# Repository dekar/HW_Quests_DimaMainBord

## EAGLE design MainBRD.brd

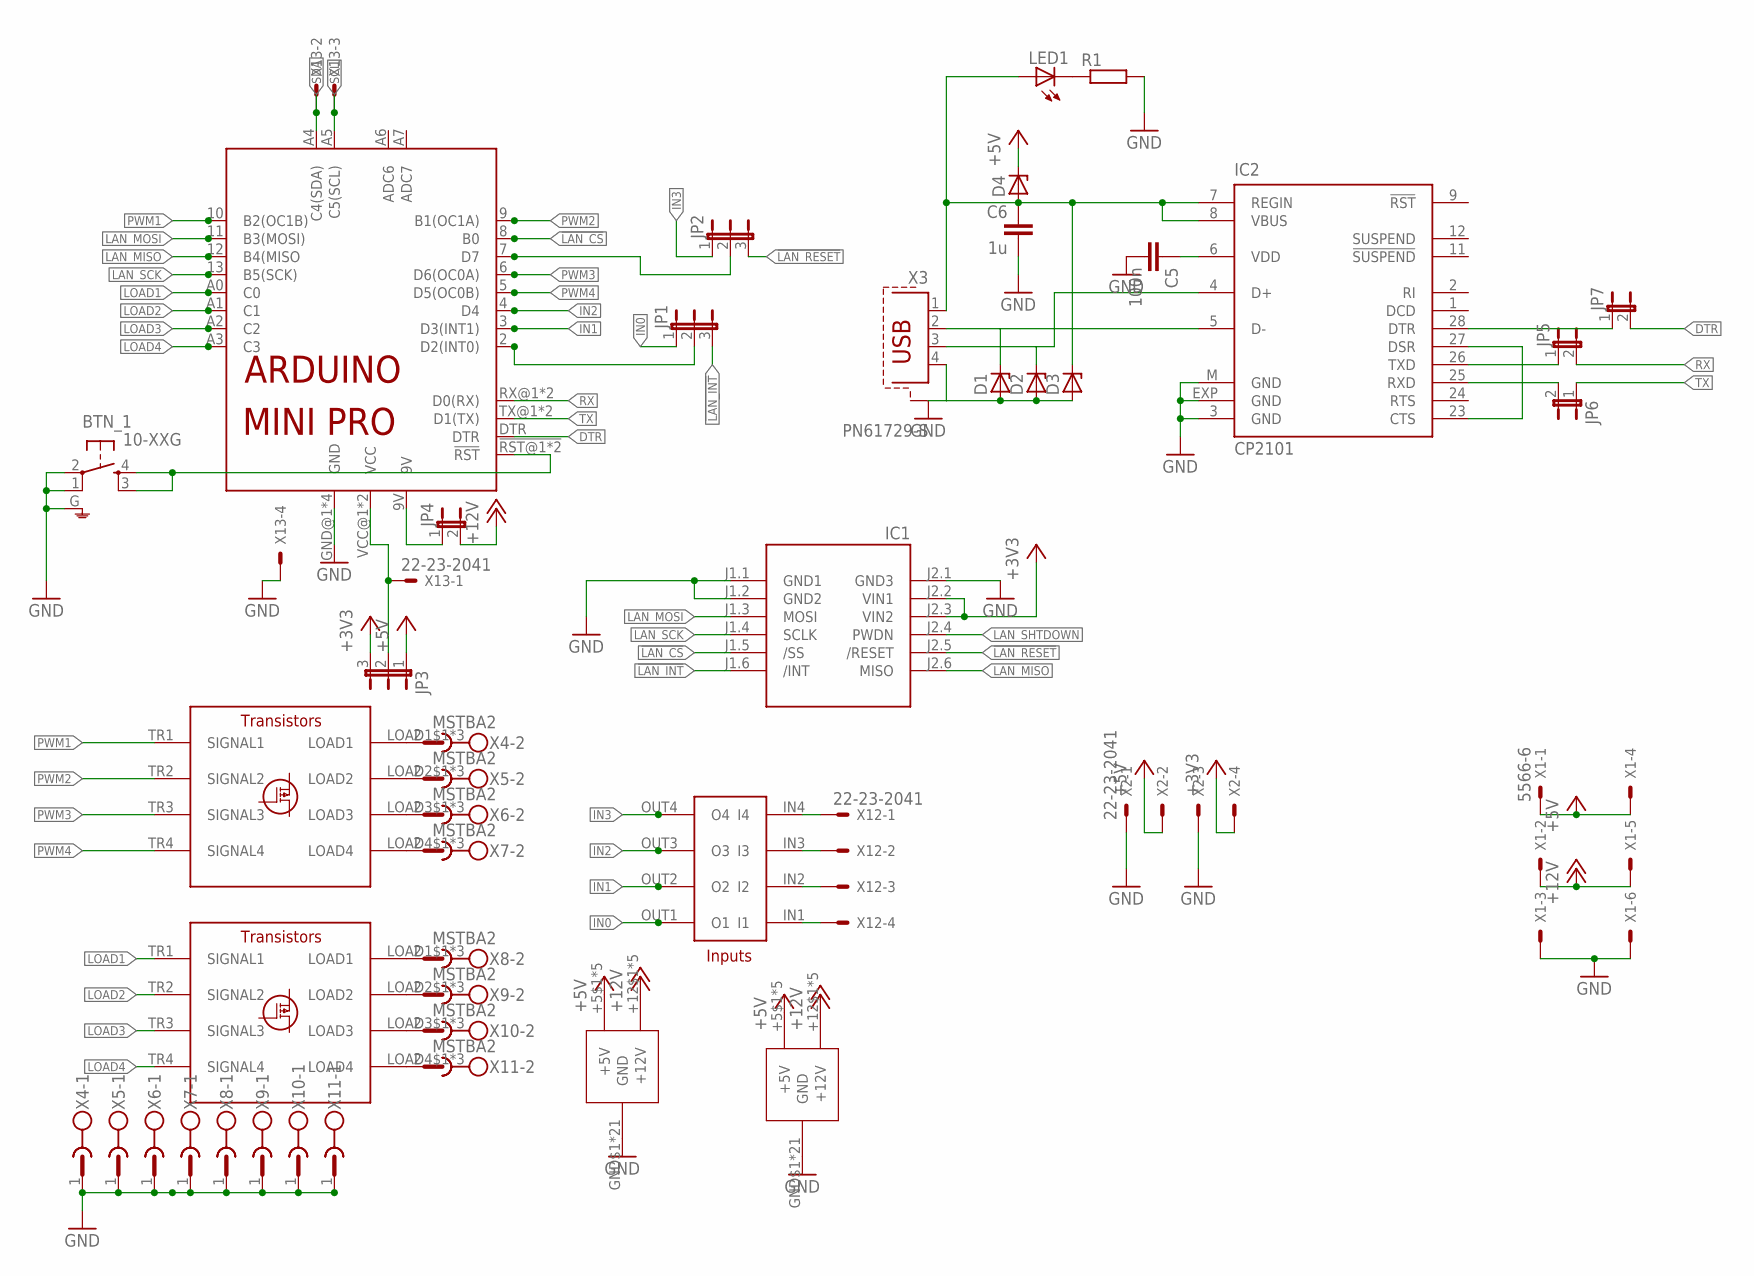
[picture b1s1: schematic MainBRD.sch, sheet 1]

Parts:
BTN_1: 10-XXG; B3F-10XXG
C5: 100n; C0805
C6: 1u; C1206
D1, D2, D3, D4: ZENER-DIODESOD80C; SOD80C
IC1: WIZ820IO_DEVICE'DUAL-IN-LINE'; WIZ820IO
IC2: CP2101; MLP28
JP1, JP2, JP3: JP2E; JP2
JP4, JP5, JP6, JP7: JP1E; JP1
LED1: LEDCHIPLED_1206; CHIPLED_1206
R1: R-EU_M0805; M0805
U$1: ARDUINO_MINI_PRO
U$2, U$3: KBLES_TRANSISTOR
X1: 5566-6
X2: 22-23-2041
X3: PN61729-S
X4: MSTBA2
X5, X6, X7, X8, X9, X10, X11: MSTBA2; MPN 1757242
X12, X13: 22-23-2041; MPN 22-23-2041

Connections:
!LAN_CS: IC1.J1.5 (/SS), U$1.8 (B0)
!LAN_INT: IC1.J1.6 (/INT), JP1.3
!LAN_RESET: IC1.J2.5 (/RESET), JP2.3
+3V3: IC1.J2.2 (VIN1), IC1.J2.3 (VIN2), JP3.3, X2.4
+5V: D4.C, JP3.1, U$2.+5$1 (+5V), U$2.+5$2 (+5V), U$2.+5$3 (+5V), U$2.+5$4 (+5V), U$2.+5$5 (+5V), U$3.+5$1 (+5V), U$3.+5$2 (+5V), U$3.+5$3 (+5V), U$3.+5$4 (+5V), U$3.+5$5 (+5V), X1.1, X1.4, X2.2
+12V: JP4.2, U$2.+12$1 (+12V), U$2.+12$2 (+12V), U$2.+12$3 (+12V), U$2.+12$4 (+12V), U$2.+12$5 (+12V), U$3.+12$1 (+12V), U$3.+12$2 (+12V), U$3.+12$3 (+12V), U$3.+12$4 (+12V), U$3.+12$5 (+12V), X1.2, X1.5
DSR/CTS: IC2.23 (CTS), IC2.27 (DSR)
DTR: JP7.2, U$1.DTR
GND: BTN_1.1, BTN_1.2, BTN_1.G (GND), C5.2, C6.2, D1.A, D2.A, D3.A, IC1.J1.1 (GND1), IC1.J1.2 (GND2), IC1.J2.1 (GND3), IC2.3 (GND), IC2.EXP (GND), IC2.M (GND), R1.2, U$1.GND@1 (GND), U$1.GND@2 (GND), U$1.GND@3 (GND), U$1.GND@4 (GND), U$2.GND$1 (GND), U$2.GND$2 (GND), U$2.GND$3 (GND), U$2.GND$4 (GND), U$2.GND$5 (GND), U$2.GND$6 (GND), U$2.GND$7 (GND), U$2.GND$8 (GND), U$2.GND$9 (GND), U$2.GND$10 (GND), U$2.GND$11 (GND), U$2.GND$12 (GND), U$2.GND$13 (GND), U$2.GND$14 (GND), U$2.GND$15 (GND), U$2.GND$16 (GND), U$2.GND$17 (GND), U$2.GND$18 (GND), U$2.GND$19 (GND), U$2.GND$20 (GND), U$2.GND$21 (GND), U$3.GND$1 (GND), U$3.GND$2 (GND), U$3.GND$3 (GND), U$3.GND$4 (GND), U$3.GND$5 (GND), U$3.GND$6 (GND), U$3.GND$7 (GND), U$3.GND$8 (GND), U$3.GND$9 (GND), U$3.GND$10 (GND), U$3.GND$11 (GND), U$3.GND$12 (GND), U$3.GND$13 (GND), U$3.GND$14 (GND), U$3.GND$15 (GND), U$3.GND$16 (GND), U$3.GND$17 (GND), U$3.GND$18 (GND), U$3.GND$19 (GND), U$3.GND$20 (GND), U$3.GND$21 (GND), X1.3, X1.6, X2.1, X2.3, X3.4, X3.SHLD@1 (S1), X3.SHLD@2 (S1), X4.1, X5.1, X6.1, X7.1, X8.1, X9.1, X10.1, X11.1, X13.4
IN0: JP1.1, U$2.OUT1 (O1)
IN1: U$1.3 (D3(INT1)), U$2.OUT2 (O2)
IN2: U$1.4 (D4), U$2.OUT3 (O3)
IN3: JP2.1, U$2.OUT4 (O4)
LAN_MISO: IC1.J2.6 (MISO), U$1.12 (B4(MISO)
LAN_MOSI: IC1.J1.3 (MOSI), U$1.11 (B3(MOSI))
LAN_SCK: IC1.J1.4 (SCLK), U$1.13 (B5(SCK))
LAN_SHTDOWN: IC1.J2.4 (PWDN)
LOAD1: U$1.A0 (C0), U$3.TR1 (SIGNAL1)
LOAD2: U$1.A1 (C1), U$3.TR2 (SIGNAL2)
LOAD3: U$1.A2 (C2), U$3.TR3 (SIGNAL3)
LOAD4: U$1.A3 (C3), U$3.TR4 (SIGNAL4)
unnamed: JP1.2, U$1.2 (D2(INT0))
unnamed: JP4.1, U$1.9V
unnamed: JP3.2, U$1.VCC@1 (VCC), U$1.VCC@2 (VCC), X13.1
unnamed: C6.1, D3.C, D4.A, IC2.7 (REGIN), IC2.8 (VBUS), LED1.A, X3.1
unnamed: JP2.2, U$1.7 (D7)
unnamed: IC2.25 (RXD), JP6.2
unnamed: D2.C, IC2.4 (D+), X3.3
unnamed: IC2.26 (TXD), JP5.1
unnamed: D1.C, IC2.5 (D-), X3.2
unnamed: IC2.28 (DTR), JP7.1
unnamed: U$2.LOAD1$1 (LOAD1), U$2.LOAD1$2 (LOAD1), U$2.LOAD1$3 (LOAD1), X4.2
unnamed: C5.1, IC2.6 (VDD)
unnamed: U$2.LOAD2$1 (LOAD2), U$2.LOAD2$2. (LOAD2), U$2.LOAD2$3 (LOAD2), X5.2
unnamed: U$2.LOAD3$1 (LOAD3), U$2.LOAD3$2 (LOAD3), U$2.LOAD3$3 (LOAD3), X6.2
unnamed: U$2.LOAD4$1 (LOAD4), U$2.LOAD4$2 (LOAD4), U$2.LOAD4$3 (LOAD4), X7.2
unnamed: LED1.C, R1.1
unnamed: U$3.LOAD1$1 (LOAD1), U$3.LOAD1$2 (LOAD1), U$3.LOAD1$3 (LOAD1), X8.2
unnamed: U$3.LOAD2$1 (LOAD2), U$3.LOAD2$2. (LOAD2), U$3.LOAD2$3 (LOAD2), X9.2
unnamed: U$3.LOAD3$1 (LOAD3), U$3.LOAD3$2 (LOAD3), U$3.LOAD3$3 (LOAD3), X10.2
unnamed: U$3.LOAD4$1 (LOAD4), U$3.LOAD4$2 (LOAD4), U$3.LOAD4$3 (LOAD4), X11.2
unnamed: U$2.IN4 (I4), X12.1
unnamed: U$2.IN3 (I3), X12.2
unnamed: U$2.IN2 (I2), X12.3
unnamed: U$2.IN1 (I1), X12.4
unnamed: BTN_1.3 (S1), BTN_1.4 (S), U$1.!RST@1 (!RST), U$1.!RST@2 (!RST)
PWM1: U$1.10 (B2(OC1B)), U$2.TR1 (SIGNAL1)
PWM2: U$1.9 (B1(OC1A)), U$2.TR2 (SIGNAL2)
PWM3: U$1.6 (D6(OC0A)), U$2.TR3 (SIGNAL3)
PWM4: U$1.5 (D5(OC0B)), U$2.TR4 (SIGNAL4)
RX: JP5.2, U$1.RX@1 (D0(RX)), U$1.RX@2 (D0(RX))
SCL: U$1.A5 (C5(SCL)), X13.3
SDA: U$1.A4 (C4(SDA)), X13.2
TX: JP6.1, U$1.TX@1 (D1(TX)), U$1.TX@2 (D1(TX))

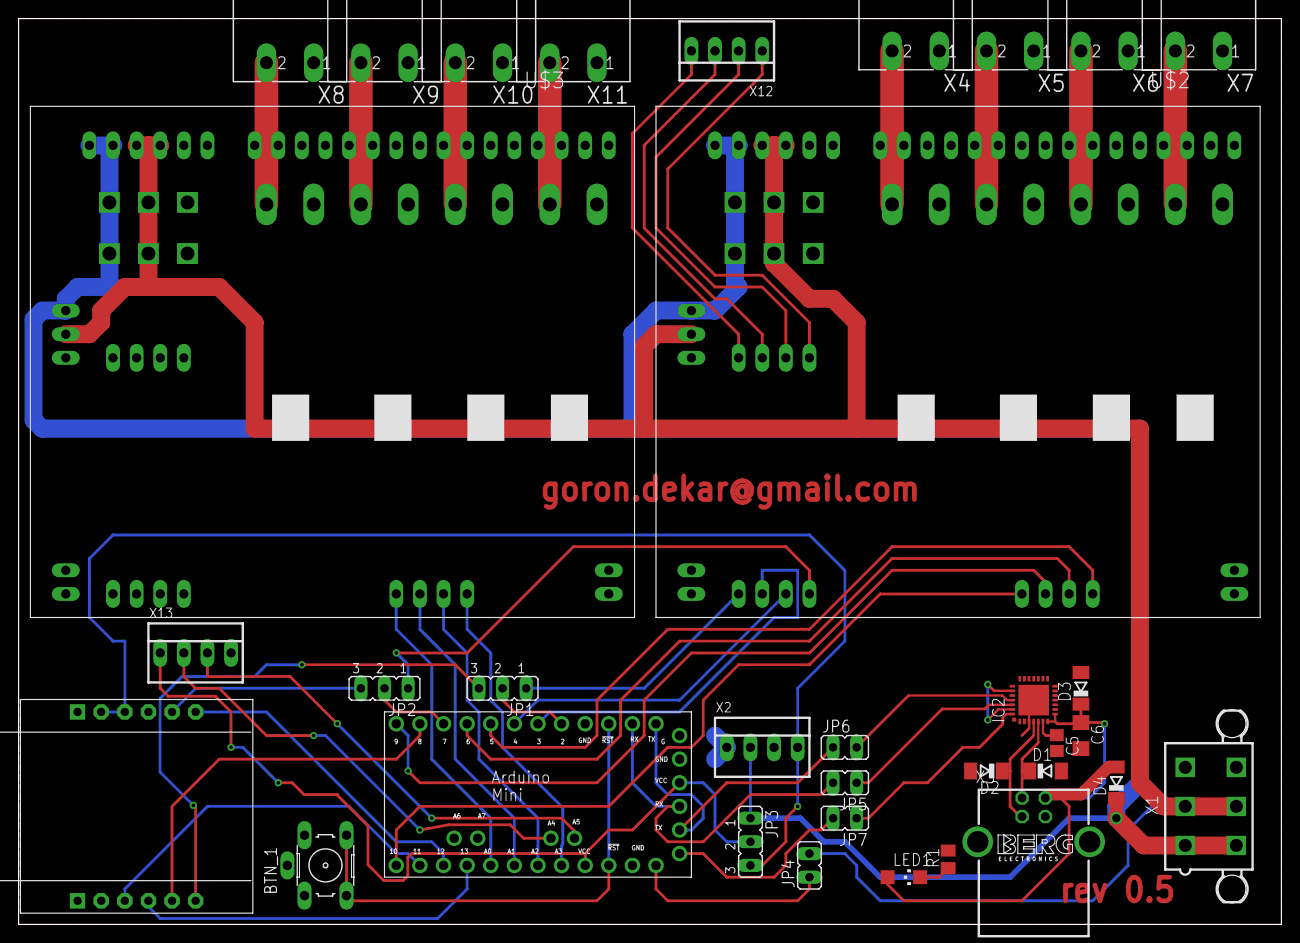
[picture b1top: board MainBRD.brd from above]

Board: 2 copper layers, 135.9 x 97.5 mm, 34 parts (0 on the bottom side), 53 nets.

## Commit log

2014-10-08 Ver 0.5
2014-10-08 Change vias to 0.4 for speed up the production
